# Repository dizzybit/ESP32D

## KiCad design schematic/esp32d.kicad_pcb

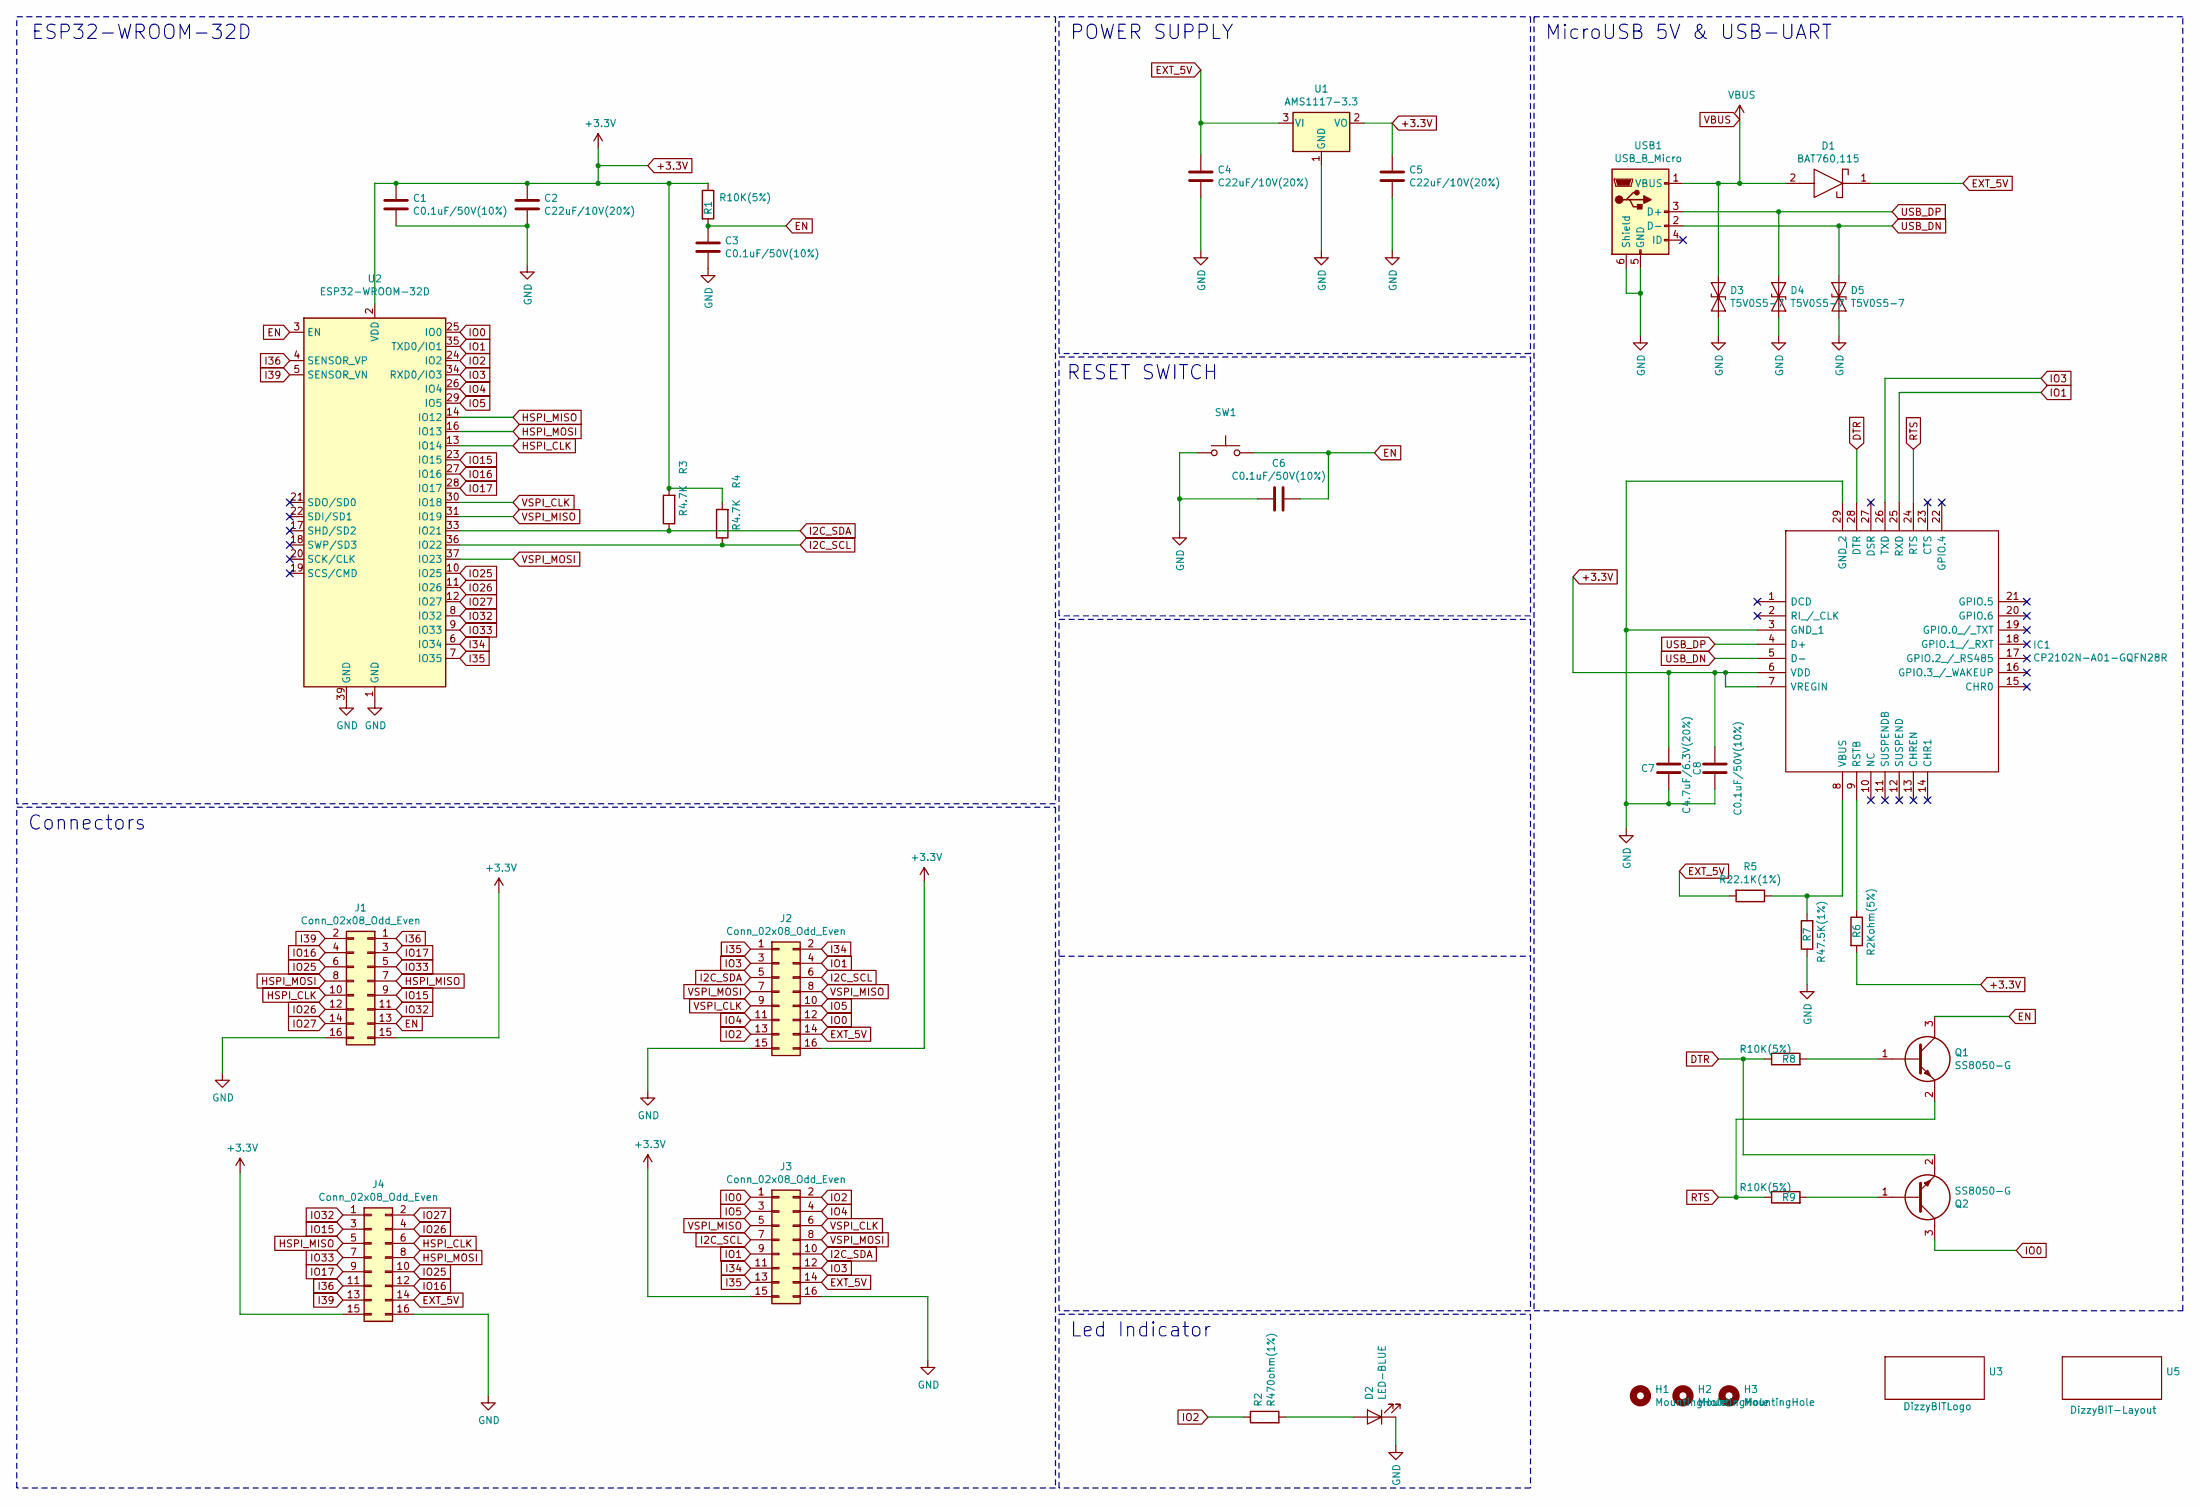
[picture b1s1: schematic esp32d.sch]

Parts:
C1, C3, C6, C8: C0.1uF/50V(10%); C_0603_1608Metric
C2, C4, C5: C22uF/10V(20%); C_0603_1608Metric
C7: C4.7uF/6.3V(20%); C_0603_1608Metric
D1: BAT760,115; SOD2513X120N
D2: LED-BLUE; LED_0805_2012Metric
D3, D4, D5: T5V0S5-7; SOD-523
H1, H2, H3: MountingHole; MountingHole_2.2mm_M2_DIN965_Pad
IC1: CP2102N-A01-GQFN28R; QFN50P500X500X80-29N-D; Mouser Part Number 634-CP2102NA01GFN28R
J1, J2: Conn_02x08_Odd_Even; PinSocket_2x08_P2.54mm_Vertical
J3, J4: Conn_02x08_Odd_Even; JST_PUD_S16B-PUDSS-1_2x08_P2.00mm_Horizontal
Q1, Q2: SS8050-G; SOT-23-3; Mouser Part Number 750-SS8050-G
R1, R8, R9: R10K(5%); R_0603_1608Metric
R2: R470ohm(1%); R_0603_1608Metric
R3, R4: R4.7K; R_0603_1608Metric
R5: R22.1K(1%); C_0603_1608Metric
R6: R2Kohm(5%); R_0603_1608Metric
R7: R47.5K(1%); C_0603_1608Metric
SW1: SW_Push; SW_Tactile_SPST_Angled_PTS645Vx31-2LFS
U1: AMS1117-3.3; SOT-223-3_TabPin2
U2: ESP32-WROOM-32D; ESP32-WROOM-32
U3: DizzyBITLogo; DizzyBIT_silk_20
U5: DizzyBIT-Layout; DizzyBit-Din Rail Module
USB1: USB_B_Micro; DS1105-12

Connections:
+3.3V: C1.2, C2.1, C5.1, C7.1, C8.1, IC1.6 (VDD), IC1.7 (VREGIN), J1.15, J2.16, J3.15, J4.15, R1.1, R3.2, R4.2, R6.2, U1.2 (VO), U2.2 (VDD)
DTR: IC1.28 (DTR), Q2.2, R8.1
EN: C3.2, C6.2, J1.13, Q1.3, R1.2, SW1.2, U2.3 (EN)
EXT_5V: C4.1, D1.1, J2.14, J3.14, J4.14, R5.2, U1.3 (VI)
GND: C1.1, C2.2, C3.1, C4.2, C5.2, C6.1, C7.2, C8.2, D2.1 (K), D3.2 (A2), D4.2 (A2), D5.2 (A2), IC1.3 (GND_1), IC1.29 (GND_2), J1.16, J2.15, J3.16, J4.16, R7.1, SW1.1, U1.1 (GND), U2.1 (GND), U2.15 (GND), U2.38 (GND), U2.39 (GND), USB1.5 (GND), USB1.6 (Shield)
HSPI_CLK: J1.10, J4.6, U2.13 (IO14)
HSPI_MISO: J1.7, J4.5, U2.14 (IO12)
HSPI_MOSI: J1.8, J4.8, U2.16 (IO13)
I2C_SCL: J2.6, J3.7, R4.1, U2.36 (IO22)
I2C_SDA: J2.5, J3.10, R3.1, U2.33 (IO21)
I34: J2.2, J3.11, U2.6 (IO34)
I35: J2.1, J3.13, U2.7 (IO35)
I36: J1.1, J4.11, U2.4 (SENSOR_VP)
I39: J1.2, J4.13, U2.5 (SENSOR_VN)
IO0: J2.12, J3.1, Q2.3, U2.25 (IO0)
IO1: IC1.25 (RXD), J2.4, J3.9, U2.35 (TXD0/IO1)
IO2: J2.13, J3.2, R2.1, U2.24 (IO2)
IO3: IC1.26 (TXD), J2.3, J3.12, U2.34 (RXD0/IO3)
IO4: J2.11, J3.4, U2.26 (IO4)
IO5: J2.10, J3.3, U2.29 (IO5)
IO15: J1.9, J4.3, U2.23 (IO15)
IO16: J1.4, J4.12, U2.27 (IO16)
IO17: J1.3, J4.9, U2.28 (IO17)
IO25: J1.6, J4.10, U2.10 (IO25)
IO26: J1.12, J4.4, U2.11 (IO26)
IO27: J1.14, J4.2, U2.12 (IO27)
IO32: J1.11, J4.1, U2.8 (IO32)
IO33: J1.5, J4.7, U2.9 (IO33)
unnamed: D2.2 (A), R2.2
unnamed: IC1.8 (VBUS), R5.1, R7.2
unnamed: IC1.9 (RSTB), R6.1
unnamed: Q1.1, R8.2
unnamed: Q2.1, R9.2
RTS: IC1.24 (RTS), Q1.2, R9.1
USB_DN: D5.1 (A1), IC1.5 (D-), USB1.2 (D-)
USB_DP: D4.1 (A1), IC1.4 (D+), USB1.3 (D+)
VBUS: D1.2, D3.1 (A1), USB1.1 (VBUS)
VSPI_CLK: J2.9, J3.6, U2.30 (IO18)
VSPI_MISO: J2.8, J3.5, U2.31 (IO19)
VSPI_MOSI: J2.7, J3.8, U2.37 (IO23)

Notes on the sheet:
ESP32-WROOM-32D
POWER SUPPLY
RESET SWITCH
MicroUSB 5V & USB-UART
Led Indicator
Connectors

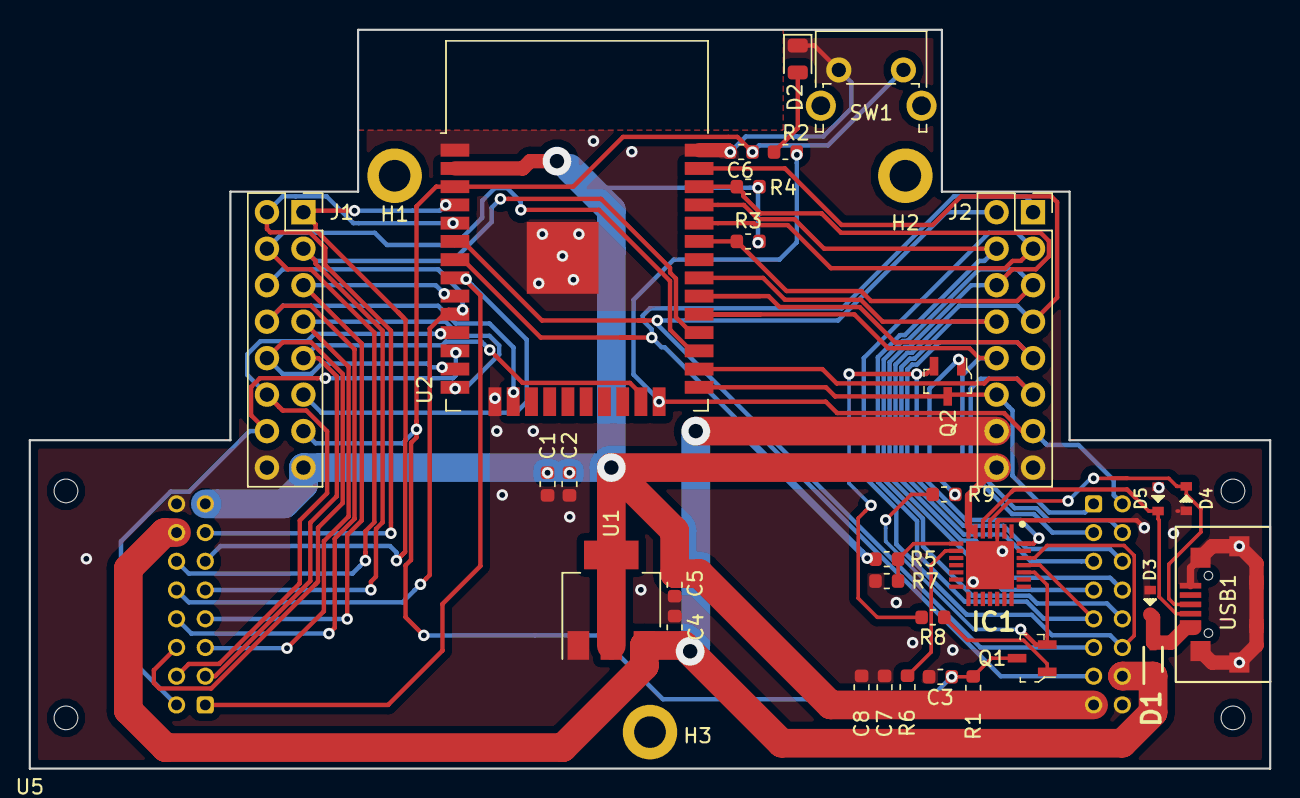
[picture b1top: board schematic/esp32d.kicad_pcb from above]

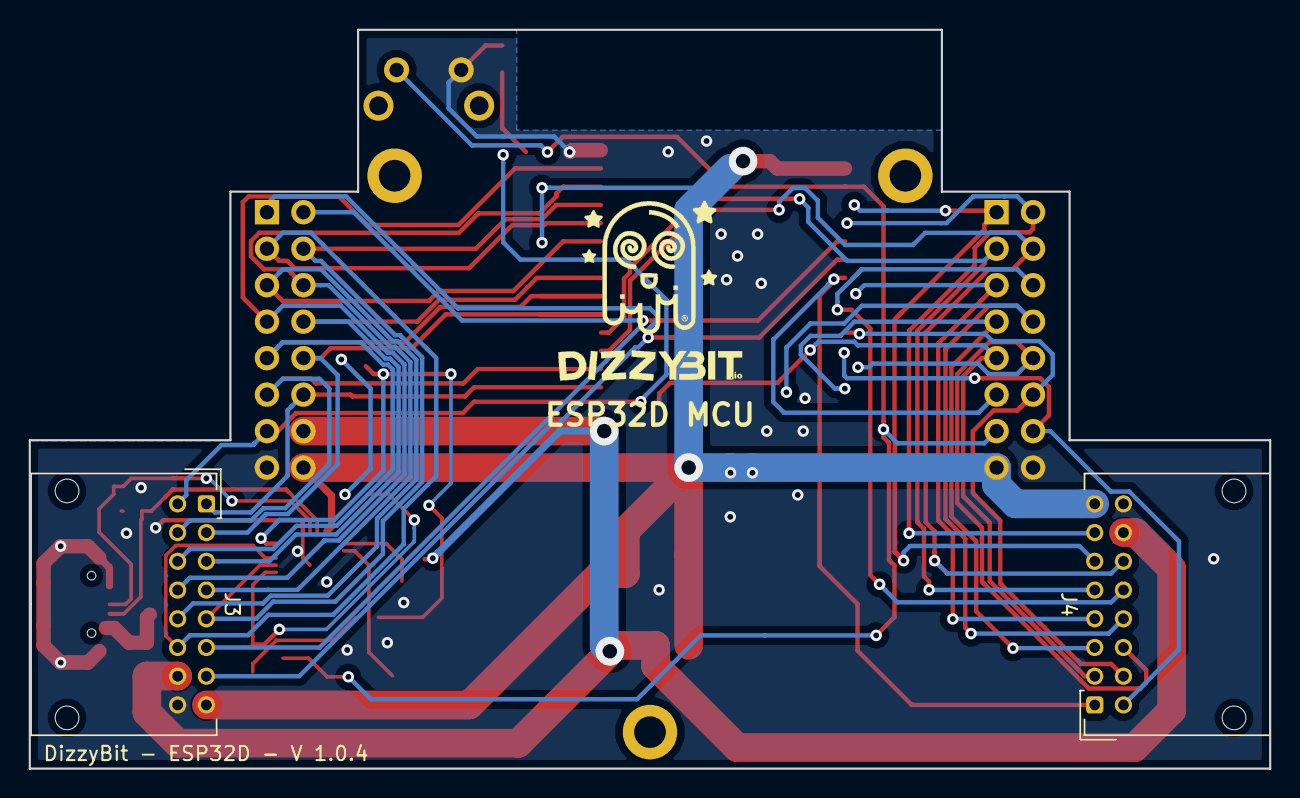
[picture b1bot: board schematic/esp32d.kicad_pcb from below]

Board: 2 copper layers, 86.4 x 51.4 mm, 38 parts (3 on the bottom side), 40 nets.

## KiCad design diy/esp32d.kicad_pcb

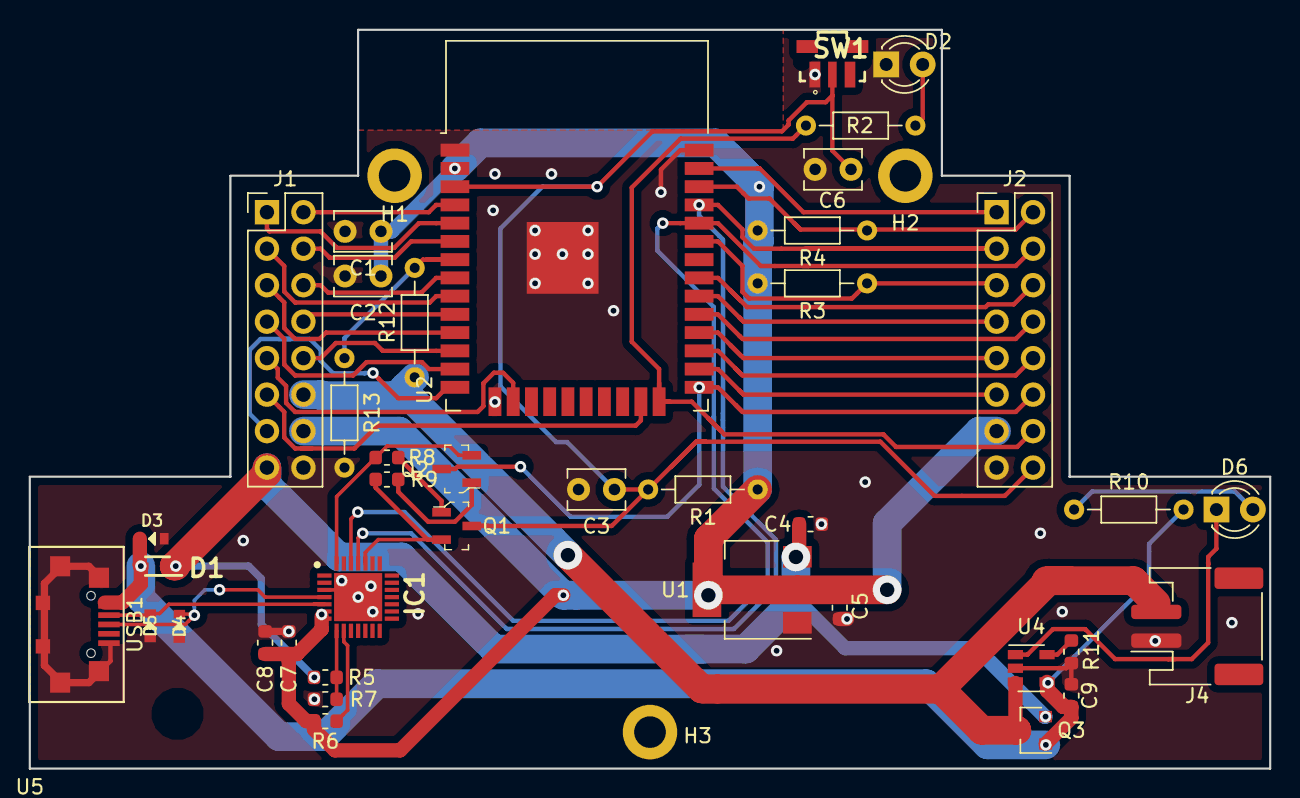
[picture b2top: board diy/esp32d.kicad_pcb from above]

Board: 2 copper layers, 86.4 x 51.4 mm, 45 parts (1 on the bottom side), 44 nets.

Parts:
C1, C3, C6: C0.1uF/50V(10%); C_Disc_D3.8mm_W2.6mm_P2.50mm
C2: C22uF/10V(10%); C_Disc_D3.8mm_W2.6mm_P2.50mm
C4, C5: C22uF/10V(20%); C_0603_1608Metric
C7, C9: C4.7uF/6.3V(20%); C_0603_1608Metric
C8: C0.1uF/50V(10%); C_0603_1608Metric
D1: BAT760,115; SOD2513X120N
D2: LED-BLUE; LED_D3.0mm
D3, D4, D5: T5V0S5-7; SOD-523
D6: LED-YELLOW; LED_D3.0mm
H1, H2, H3: MountingHole; MountingHole_2.2mm_M2_DIN965_Pad
IC1: CP2102N-A01-GQFN28R; QFN50P500X500X80-29N-D
J1, J2: Conn_02x08_Odd_Even; PinHeader_2x08_P2.54mm_Vertical
J4: Conn_01x02; JST_PH_S2B-PH-SM4-TB_1x02-1MP_P2.00mm_Horizontal
Q1, Q2: SS8050-G; SOT-23-3
Q3: DMG2307L-7; SOT-23
R1: R10K(5%); R_Axial_DIN0204_L3.6mm_D1.6mm_P7.62mm_Horizontal
R2: R470ohm(1%); R_Axial_DIN0204_L3.6mm_D1.6mm_P7.62mm_Horizontal
R3, R4: R4.7K; R_Axial_DIN0204_L3.6mm_D1.6mm_P7.62mm_Horizontal
R5: R22.1K(1%); C_0603_1608Metric
R6: R2Kohm(5%); R_0603_1608Metric
R7: R47.5K(1%); C_0603_1608Metric
R8, R9: R10K(5%); R_0603_1608Metric
R10: R1K; R_Axial_DIN0204_L3.6mm_D1.6mm_P7.62mm_Horizontal
R11: R4.7K; R_0603_1608Metric
R12, R13: R100K; R_Axial_DIN0204_L3.6mm_D1.6mm_P7.62mm_Horizontal
SW1: SW_Push; TL3340
U1: AMS1117-3.3; SOT-223-3_TabPin2
U2: ESP32-WROOM-32D; ESP32-WROOM-32
U3: DizzyBITLogo; DizzyBIT_silk_20
U4: MCP73831-2-OT; SOT-23-5
U5: DizzyBIT-Layout; DizzyBit-Din Rail Module
USB1: USB_B_Micro; DS1105-12

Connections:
+3.3V: C1.1, C2.1, C5.1, C7.1, C8.1, IC1.6, IC1.7, J1.14, J2.13, R1.1, R3.2, R4.2, R6.2, U1.2, U2.2
DTR: IC1.28, Q2.2, R8.1
EN: C3.1, C6.2, J2.16, Q1.3, R1.2, SW1.2, U2.3
EXT_5V: C4.1, D1.1, J1.15, Q3.2, R5.2, U1.3
GND: C1.2, C2.2, C3.2, C4.2, C5.2, C6.1, C7.2, C8.2, C9.2, D2.1, D3.2, D4.2, D5.2, IC1.3, IC1.29, J1.16, J2.15, J4.1, R7.1, R11.1, R13.2, SW1.1, U1.1, U2.1, U2.15, U2.38, U2.39, U4.2, USB1.5, USB1.6
HSPI_CLK: J1.7, U2.13
HSPI_MISO: J1.13, U2.14
HSPI_MOSI: J1.9, U2.16
I2C_SCL: J2.2, R4.1, U2.36
I2C_SDA: J2.5, R3.1, U2.33
I34: J1.4, U2.6
I35: R12.2, R13.1, U2.7
I36: J1.2, U2.4
I39: J1.1, U2.5
IO0: J2.12, Q2.3, U2.25
IO1: IC1.25, J2.3, U2.35
IO2: J2.14, R2.1, U2.24
IO3: IC1.26, J2.4, U2.34
IO4: J2.11, U2.26
IO5: J2.8, U2.29
IO15: J1.11, U2.23
IO16: J2.10, U2.27
IO17: J2.9, U2.28
IO25: J1.8, U2.10
IO26: J1.5, U2.11
IO27: J1.10, U2.12
IO32: J1.6, U2.8
IO33: J1.3, U2.9
unnamed: D2.2, R2.2
unnamed: D6.1, U4.1
unnamed: D6.2, R10.1
unnamed: IC1.8, R5.1, R7.2
unnamed: IC1.9, R6.1
unnamed: Q1.1, R8.2
unnamed: Q2.1, R9.2
unnamed: R11.2, U4.5
RTS: IC1.24, Q1.2, R9.1
USB_DN: D5.1, IC1.5, USB1.2
USB_DP: D4.1, IC1.4, USB1.3
VBAT: J1.12, J4.2, Q3.3, R12.1, U4.3
VBUS: C9.1, D1.2, D3.1, Q3.1, R10.2, U4.4, USB1.1
VSPI_CLK: J2.7, U2.30
VSPI_MISO: J2.6, U2.31
VSPI_MOSI: J2.1, U2.37

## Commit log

2019-09-27 ESP32D for DIN rail with Li-Po charger
2019-09-27 Added 100K resistors part number
2019-09-27 Added Standard module design
    Added Part numbers
    Modified footprint positions to match standard module design
2019-09-27 Optimized thermal dissipation
2019-09-30 Repositioned LEDs to match the standard module design
2019-10-02 Changed 3.3V position for better PCB exposure
2019-10-02 Changed EN and IO2 position
2019-10-02 Changed blue led PN for 3.3V
    Added DIY project folder
2019-10-02 Added DIY board
2019-10-03 Finished the DIY board
2019-10-04 Added 3d and Gerber files
    Moved DIY project to a stand-alone project
2019-12-20 Major Update. Changed pin configuration and board outline.
